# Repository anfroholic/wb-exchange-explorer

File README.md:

# wirebond.svg: a viewable wire bond exchange format

wirebond.svg is a restricted SVG profile for describing a wire bonded assembly. A `.wb.svg` file opens in any browser as a true-scale bonding diagram, and tools read the same file as data.

**Status: prototype, v0.1 draft.** All example data is illustrative. Nothing here has been run through a real bonder or offline programming tool.

**Name:** this project is called wirebond.svg, and its files use the extension `.wb.svg`. It was previously called WBX, and the code still uses that name (`wbx.py`, the `wbx` package and `urn:wbx:0.1`) until it is renamed. The repository also still has its old name, `wb-exchange-explorer`.

## The idea

- The picture is the data: 1 SVG unit = 1 µm, `stroke-width` is wire diameter, `rect` is a pad opening.
- Height lives in a drawn section view, where a rectangle's height is that layer's thickness.
- Everything else sits on drawn elements as `wb:` attributes.
- Loop shapes are parametric, so one profile fits any wire span.
- Wires reference pads by name, and a checker catches geometry that has drifted.

See [SPEC.md](SPEC.md) for the format and [docs/report.md](docs/report.md) for the design reasoning and prior-art survey.

New to wire bonding? Open [docs/primer/wire-bonding-primer.html](docs/primer/wire-bonding-primer.html) in a browser. It explains what bonding is, the words for it, and why each design rule is what it is. [docs/primer/fiducials.html](docs/primer/fiducials.html) covers how pick and place machines and wire bonders find the board and the die, and how wirebond.svg describes fiducials.

## Wire Bond Bench

Open `app/index.html` to try ways of building a bonded assembly on your own files. It reads GDS, `.kicad_pcb` and `.kicad_mod`, compares ways of generating wires, and writes back to KiCad. See [app/README.md](app/README.md).

## Try it

```sh
pip install lxml ezdxf gdstk pytest
python wbx.py check examples/example.wb.svg
python wbx.py place examples/example.wb.svg   # how far the die can move before a check fails
python wbx.py export examples/example.wb.svg /tmp/example
python examples/make_example.py   # rebuilds the example from a generated GDS
python -m pytest
```

Open `examples/example.wb.svg` in a browser and hover over any wire, pad or layer.

## What works

| Path | State |
|---|---|
| GDS to `.wb.svg` | Pad extraction tested on a generated GDS; the assembly side is hard-coded in `examples/make_example.py` |
| App to `.wb.svg` | The app in `app/` writes one from any session. Its example passes `wbx.py check`; a turned die or several die aren't read by `wbx.py` yet |
| Parse and rewrite | Byte-identical on the example |
| Checks | Bond on pad, net agreement, wire diameter, loop against cap, die edge clearance, plan-view wire gap, lands clear of the die attach |
| Die placement tolerance | Draft: datums, a profile tolerance on the die in three trial forms, and every check rerun at the edges of the zone. See [SPEC.md](SPEC.md#placement-tolerance-draft) |
| Bondlist CSV and 3D DXF export | Generated; not loaded in a bonder tool |
| KiCad import and export | Not built |

Known limits of the prototype: one die, a fixed canvas size, µm and percent moves only (no angles), and a plan-view wire gap check that doesn't yet account for loop height.

## Handling files

Do not run `.wb.svg` files through SVGO or other minifiers. They convert shapes to paths and remove `id` values, which breaks parsing. Editing in Inkscape, Illustrator or Figma is untested.

## Related work

[open.cob.json](https://github.com/MaxClerkwell/open.cob.json) is a JSON exchange format for chip-on-board wire bonding with a broader data model and working KiCad export. This project overlaps with it, and the report recommends contributing the viewable SVG form there rather than competing.

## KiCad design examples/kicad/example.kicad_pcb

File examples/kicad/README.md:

# KiCad example

The same assembly as `../example.wb.svg`, as a KiCad 10 board. It's the input a future KiCad to wirebond.svg importer would read. No importer exists yet. For now `../make_kicad.py` generates these files from the `.wb.svg`, so don't hand-edit them if you plan to regenerate.

KiCad has no bond wire, so this board uses a convention. KiCad preserves that data but doesn't interpret it.

There's no schematic, only `.kicad_pro` and `.kicad_pcb`. Nets exist only as pad assignments, so there's no ERC, and schematic parity checks and Update PCB from Schematic can't be used.

## Units

KiCad mm = SVG µm / 1000, with no offset. Both are y-down. Text values in `wb_` board properties stay in µm, as `wb_units` says.

## Mapping

| wirebond.svg | KiCad object | Where the data is |
|---|---|---|
| Die | Footprint `U1`, anchored at the GDS origin | `(at)` is the translate; `wb_gds_cell`, `wb_pad_layer` |
| Die outline | `fp_rect` on `F.Fab` in `U1` | Width and height |
| Pad | `smd rect` pad on `F.Cu` in `U1` | Number is the GDS pad name; local position is `(gds_x, -gds_y) / 1000`; size is the opening; net |
| Land | One-pad footprint `L1`..`L20`, anchored at the land centre | Pad size and net; `wb_finish` |
| Wire | Padless footprint `W01`..`W21`, anchored at the first bond | One `fp_line` on `Wirebond`, whose end is the second bond and whose width is the diameter; `wb_from`, `wb_to`, `wb_profile`, `wb_seq`, `wb_tier`, `wb_net` |
| Board fiducial | Footprint `F1`, `F2`, `P1`, anchored at the reference point | One unnumbered pad on `F.Cu` and `F.Mask`, mask opened by `wb_rule_fid_clear`; `wb_role`, `wb_datum`. An `align` fiducial's pad has `(property pad_prop_fiducial_glob)`, which KiCad writes into the Gerbers |
| Die fiducial | Not carried | It's die artwork, so it stays with the GDS |
| Substrate outline | `gr_rect` on `Edge.Cuts` | Name in `wb_substrate_name` |
| Design, rev, rules | Board properties | `wb_design`, `wb_rev`, `wb_rule_wire_gap`, `wb_rule_edge_clear`, `wb_rule_fid_clear`, plus `wb_version`, `wb_units` |
| Loop profile | Board properties | `wb_profile_<i>_name`, `_material`, `_d`, `_style`, `_dir`, `_moves`, `_interp`, `_ref_span` |
| Stack layer | Board properties | `wb_stack_<i>_name`, `_role`, `_material`, `_z`, `_t`, `_x`, `_w` |

Each die, land, wire and fiducial footprint has `wb_kind` set to `die`, `land`, `wire` or `fiducial`. A reader should select on that, and ignore other footprints.

The example's fiducials are 500 µm and 300 µm dots, sized for a bonder's camera. Pick and place guides ask for at least 1 mm, so these aren't SMT fiducials.

## For anyone reading the file

- `Wirebond` is a display name. The layer table says `(39 "User.1" user "Wirebond")`, and objects say `(layer "User.1")`. Look the name up in the table.
- KiCad re-sorts footprints and board properties when it saves. Sort wires by `wb_seq`; `<i>` keeps the profile and stack order.
- Apply the footprint's `(at x y angle)` to local coordinates. A rotated wire keeps its original local coordinates.
- A die rotated in KiCad has no equivalent in `wbx.rd`, which accepts only a translate and flip.

## Keep the project file

Board properties are repeated in `text_variables` in `example.kicad_pro`, and the two must match. KiCad's `BOARD.SynchronizeProperties()` replaces the board's table with the project's, so an empty project table erases every board property. The generator writes both tables.

To change a board value in the GUI, use Board Setup > Text Variables. The title block shows `${wb_design}` and `${wb_rev}` from the same table.

## What KiCad understands

| KiCad does | KiCad doesn't |
|---|---|
| Keep pad nets, draw the ratsnest, and check copper clearance | Know a wire connects a pad to a land |
| Keep the custom properties and let you edit them | Validate them, or check them against pads and lands |
| Draw and plot wires on `Wirebond` | Run DRC on wires, or apply the wire gap and edge clearance rules |
| Keep the profile and stack values as text | Use them; there are no 3D wires, loops or die heights |

## Expected behaviour

- **DRC:** 0 violations and 23 unconnected items. Those are real from KiCad's point of view, because wires aren't copper. A net with one pad and one land gives one line, so the 2 VBUS wires share 1. GND gives 7, and 3 of those run between die pads and match no wire.
- **Moving items:** moving `U1` or a land leaves the wires behind, and nothing in KiCad flags it. `wbx check` will, once an importer has produced a `.wb.svg`.
- **Gerbers:** die pads are on `F.Cu`, so they plot as substrate copper. Don't send this board's outputs to a fab as they are.

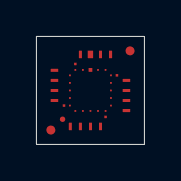
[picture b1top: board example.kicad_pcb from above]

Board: 2 copper layers, 6.0 x 6.0 mm, 45 parts (0 on the bottom side), 17 nets, no tracks yet.

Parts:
F1, F2: fiducial
L1, L2, L3, L4, L5, L6, L7, L8, L9, L10, L11, L12, L13, L14, L15, L16, L17, L18, L19, L20: land
P1: fiducial
U1: EXAMPLE_DIE; die
W01, W02, W03, W04, W05, W06, W07, W08, W09, W10, W11, W12, W13, W14, W15, W16, W17, W18, W19, W20, W21: wire

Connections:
A0: L2.1, U1.2
A1: L3.1, U1.3
A2: L4.1, U1.4
A3: L5.1, U1.5
B0: L7.1, U1.7
B2: L9.1, U1.9
B3: L10.1, U1.10
C0: L12.1, U1.12
C1: L13.1, U1.13
C2: L14.1, U1.14
C3: L15.1, U1.15
D0: L17.1, U1.17
D1: L18.1, U1.18
D2: L19.1, U1.19
D3: L20.1, U1.20
GND: L1.1, L6.1, L11.1, L16.1, U1.1, U1.6, U1.11, U1.16
VBUS: L8.1, U1.8
